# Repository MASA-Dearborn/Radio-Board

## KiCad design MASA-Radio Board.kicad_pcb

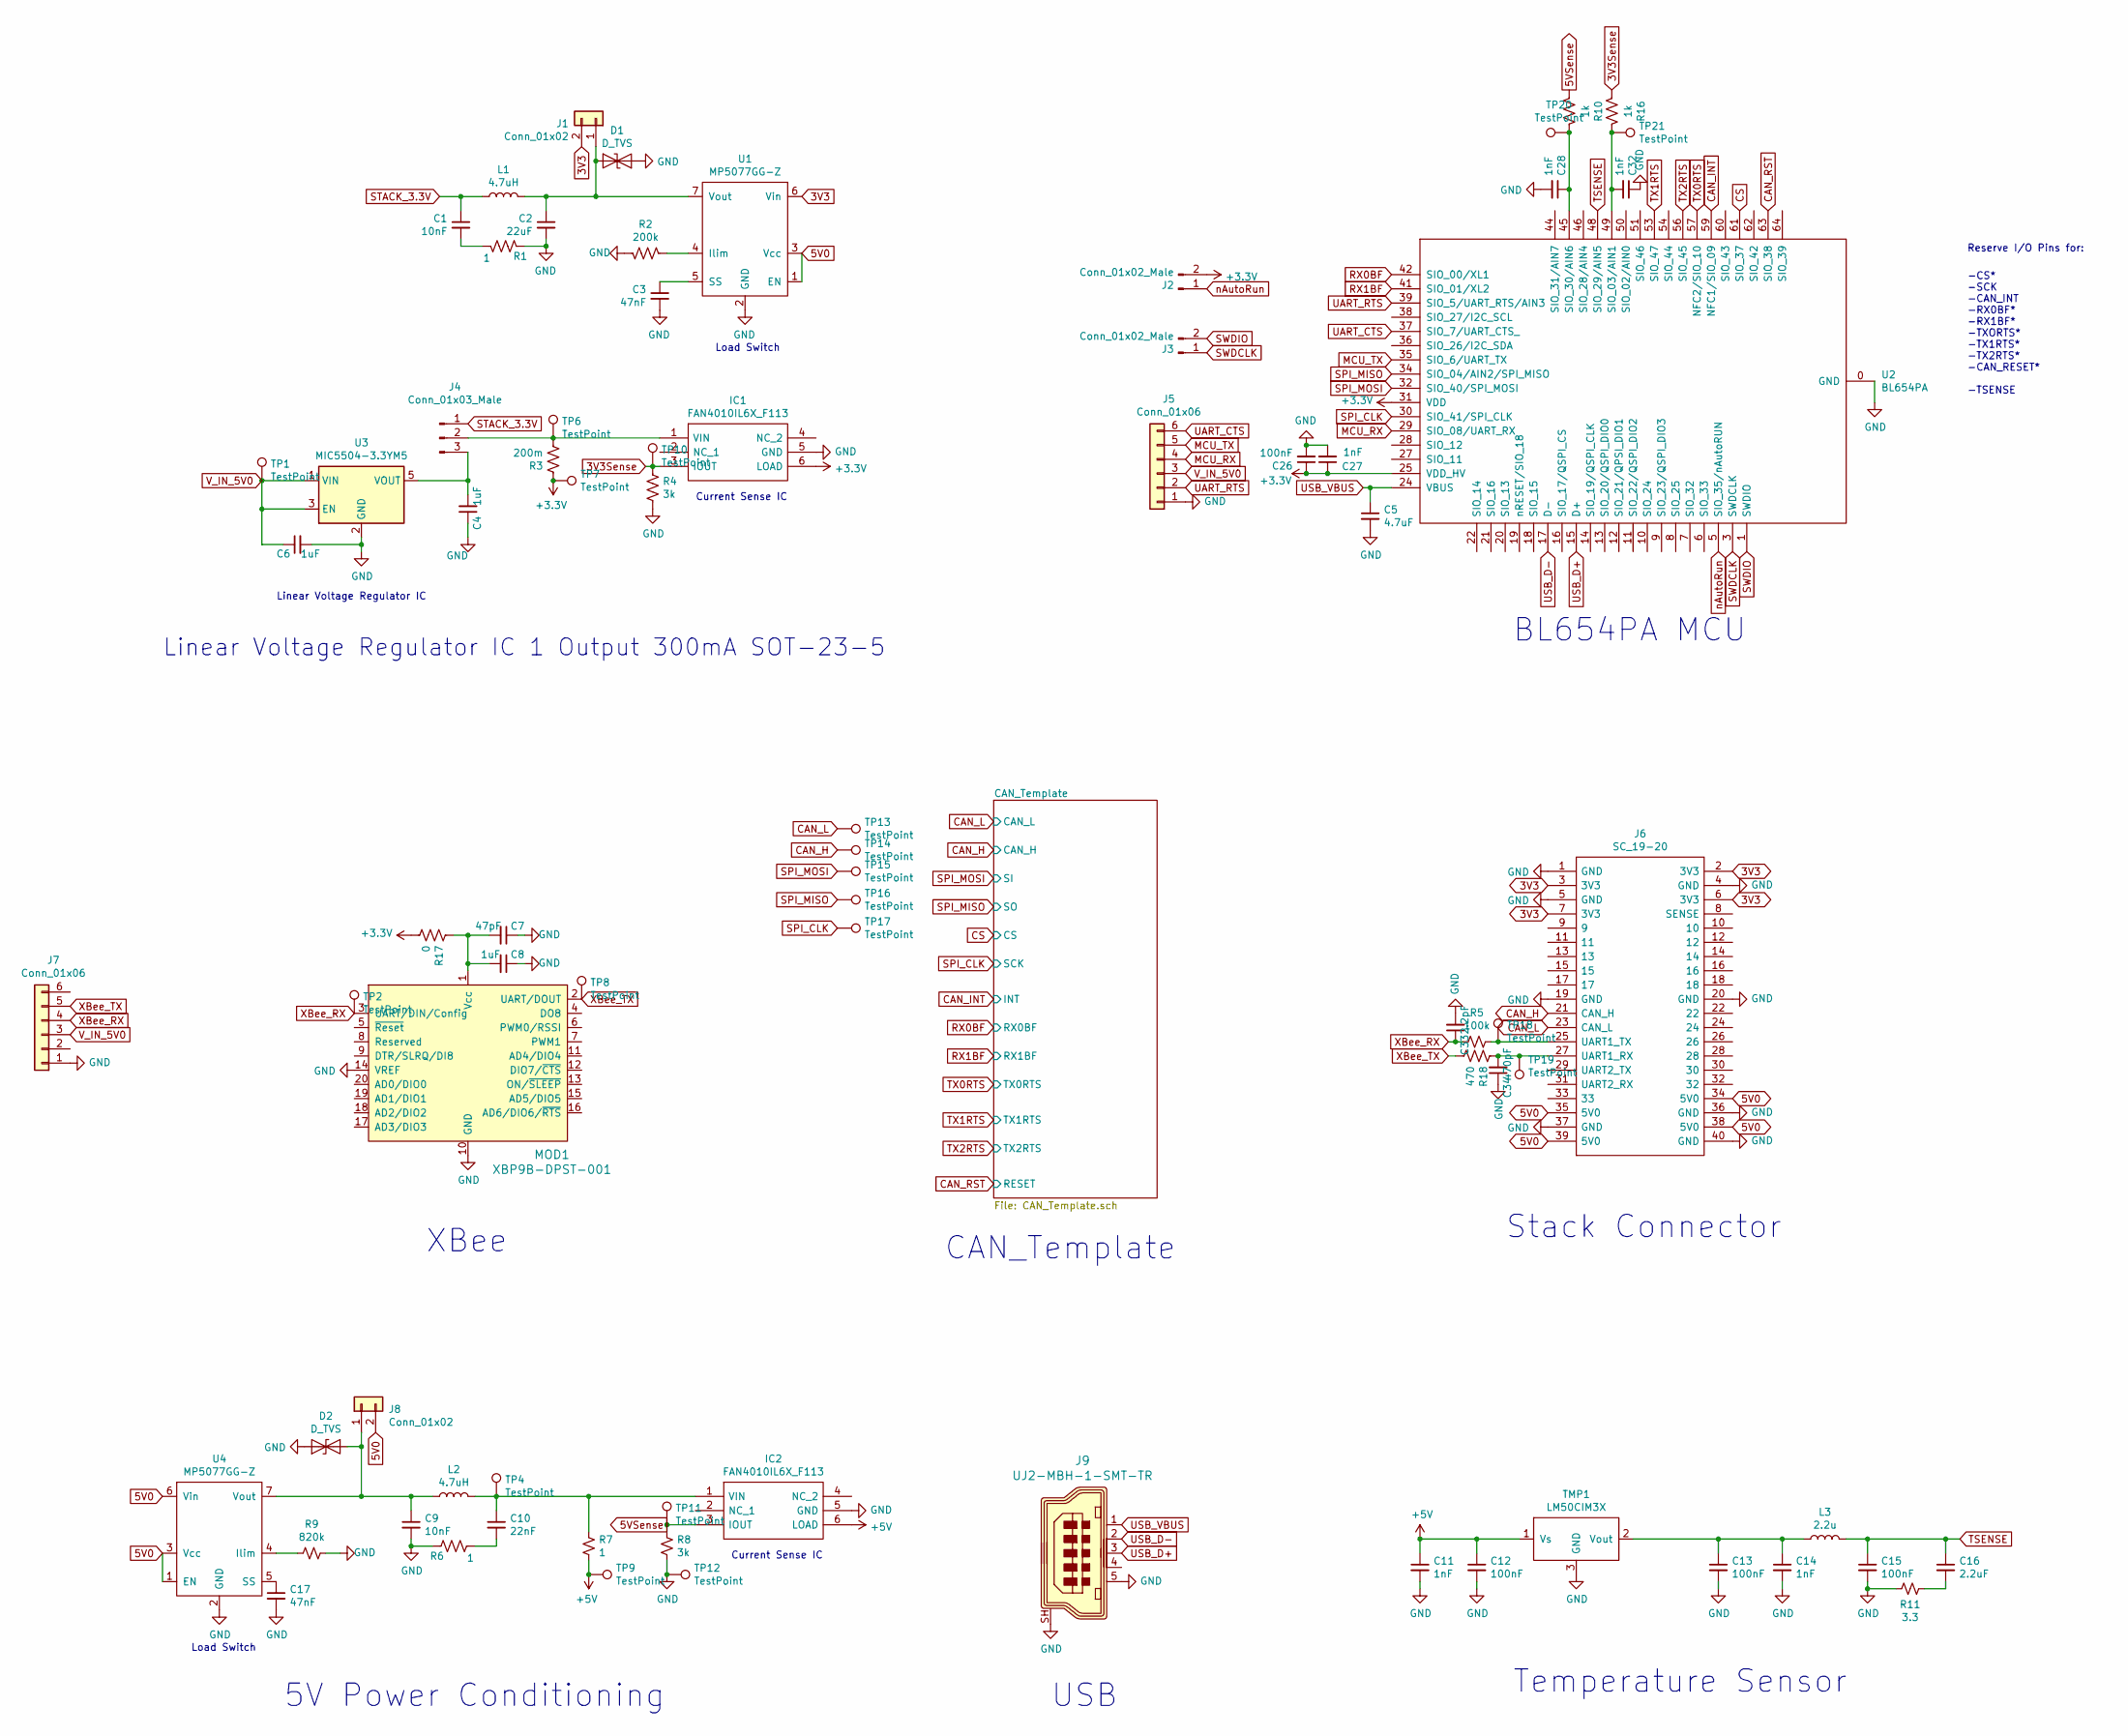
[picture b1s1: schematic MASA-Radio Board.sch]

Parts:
C1, C9: 10nF; C_0402_1005Metric
C2: 22uF; C_0603_1608Metric
C3, C17: 47nF; C_0603_1608Metric
C4, C6, C8: 1uF; C_0603_1608Metric
C5: 4.7uF; C_0603_1608Metric
C7: 47pF; C_0603_1608Metric
C10: 22nF; C_0603_1608Metric
C11, C14, C27: 1nF; C_0603_1608Metric
C12, C13, C15, C26: 100nF; C_0603_1608Metric
C16: 2.2uF; C_0603_1608Metric
C28, C32: 1nF; C_0402_1005Metric
C33: 2.2pF; C_0603_1608Metric
C34: 470pF; C_0603_1608Metric
D1, D2: D_TVS; D_SOD-523
IC1, IC2: FAN4010IL6X_F113; 6-LEAD_MICROPAK; Manufacturer_Part_Number FAN4010IL6X_F113; Mouser Part Number 512-FAN4010IL6X_F113
J1, J8: Conn_01x02; SolderJumper-2_P1.3mm_Open_TrianglePad1.0x1.5mm
J2, J3: Conn_01x02_Male; PinHeader_1x02_P2.54mm_Vertical
J4: Conn_01x03_Male; PinHeader_1x03_P2.54mm_Vertical
J5, J7: Conn_01x06; PinHeader_1x06_P2.54mm_Vertical
J6: SC_19-20; Stack_Connector_2019_2020; Manufacturer_Part_Number TFC-120-32-F-D-A-K-TR
J9: UJ2-MBH-1-SMT-TR; USB_Mini_B_Female_UJ2-MBH-1-SMT-TR; MPN UJ2-MBH-1-SMT-TR; Digi-Key_PN 102-4003-1-ND
L1, L2: 4.7uH; L_0805_2012Metric
L3: 2.2u; L_0603_1608Metric
MOD1: XBP9B-DPST-001; XBEE_PRO-20_THT; MPN XBP9B-DPST-001; Digi-Key_PN 602-1349-ND
R1, R7: 1; R_0603_1608Metric
R2: 200k; R_0603_1608Metric
R3: 200m; R_0603_1608Metric
R4, R8: 3k; R_0603_1608Metric
R5: 100k; R_0603_1608Metric
R6: 1; R_0402_1005Metric
R9: 820k; R_0603_1608Metric
R10, R16: 1k; R_0402_1005Metric
R11: 3.3; R_0603_1608Metric
R17: 0; R_0603_1608Metric
R18: 470; R_0603_1608Metric
TMP1: LM50CIM3X; SOT-23
TP1, TP2, TP4, TP6, TP7, TP8, TP9, TP10, TP11, TP12, TP13, TP14, TP15, TP16, TP17, TP18, TP19, TP20, TP21: TestPoint; TestPoint_Pad_1.0x1.0mm
U1, U4: MP5077GG-Z
U2: BL654PA
U3: MIC5504-3.3YM5; SOT-23-5

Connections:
3V3: J1.2, J6.2 (3V3), J6.3 (3V3), J6.6 (3V3), J6.7 (3V3), U1.6 (Vin), U1.11 (Vin)
3V3Sense: IC1.3 (IOUT), R4.1, R16.1, TP10.1
5V0: J6.34 (5V0), J6.35 (5V0), J6.38 (5V0), J6.39 (5V0), J8.2, U1.1 (EN), U1.3 (Vcc), U4.1 (EN), U4.3 (Vcc), U4.6 (Vin), U4.11 (Vin)
5VSense: IC2.3 (IOUT), R8.1, R10.1, TP11.1
CAN_H: J6.21 (CAN_H), TP14.1; also elsewhere on the board
CAN_INT: U2.59 (NFC1/SIO_09); also elsewhere on the board
CAN_L: J6.23 (CAN_L), TP13.1; also elsewhere on the board
CAN_RST: U2.63 (SIO_38); also elsewhere on the board
CS: U2.61 (SIO_37); also elsewhere on the board
GND: C2.2, C3.2, C4.1, C5.2, C6.2, C7.1, C8.1, C9.2, C11.2, C12.2, C13.2, C14.2, C15.2, C17.2, C26.2, C27.2, C28.2, C32.1, C33.2, C34.1, D1.1 (A1), D2.1 (A1), IC1.5 (GND), IC2.5 (GND), J5.1, J6.1 (GND), J6.4 (GND), J6.5 (GND), J6.19 (GND), J6.20 (GND), J6.36 (GND), J6.37 (GND), J6.40 (GND), J7.1, J9.5, J9.SH, MOD1.10 (GND), MOD1.14 (VREF), R1.1, R2.1, R4.2, R6.1, R8.2, R9.1, R11.1, TMP1.3 (GND), TP12.1, U1.2 (GND), U2.0 (GND), U2.23 (GND), U2.26 (GND), U2.33 (GND), U2.40 (GND), U2.43 (GND), U2.47 (GND), U2.52 (GND), U2.55 (GND), U2.58 (GND), U2.65 (GND), U2.66 (GND), U2.67 (GND), U2.68 (GND), U2.69 (GND), U2.70 (GND), U2.71 (GND), U2.72 (GND), U2.73 (GND), U2.74 (GND), U2.75 (GND), U2.76 (GND), U2.77 (GND), U2.78 (GND), U2.79 (GND), U3.2 (GND), U4.2 (GND); also elsewhere on the board
MCU_RX: J5.4, U2.29 (SIO_08/UART_RX)
MCU_TX: J5.5, U2.35 (SIO_6/UART_TX)
unnamed: C1.2, R1.2
unnamed: C2.1, D1.2 (A2), J1.1, L1.1, U1.7 (Vout), U1.8 (Vout), U1.9 (Vout), U1.10 (Vout)
unnamed: C3.1, U1.5 (SS)
unnamed: C4.2, J4.3, U3.5 (VOUT)
unnamed: C7.2, C8.2, MOD1.1 (Vcc), R17.1
unnamed: C9.1, D2.2 (A2), J8.1, L2.1, U4.7 (Vout), U4.8 (Vout), U4.9 (Vout), U4.10 (Vout)
unnamed: C10.1, IC2.1 (VIN), L2.2, R7.1, TP4.1
unnamed: C10.2, R6.2
unnamed: C13.1, C14.1, L3.1, TMP1.2 (Vout)
unnamed: C16.2, R11.2
unnamed: C17.1, U4.5 (SS)
unnamed: C28.1, R10.2, TP20.1, U2.45 (SIO_30/AIN6)
unnamed: C32.2, R16.2, TP21.1, U2.49 (SIO_03/AIN1)
unnamed: C34.2, J6.27 (UART1_RX), R18.1, TP19.1
unnamed: IC1.1 (VIN), J4.2, R3.2, TP6.1
unnamed: J6.25 (UART1_TX), R5.1, TP18.1
unnamed: R2.2, U1.4 (Ilim)
unnamed: R9.2, U4.4 (Ilim)
RX0BF: U2.42 (SIO_00/XL1); also elsewhere on the board
RX1BF: U2.41 (SIO_01/XL2); also elsewhere on the board
SPI_CLK: TP17.1, U2.30 (SIO_41/SPI_CLK); also elsewhere on the board
SPI_MISO: TP16.1, U2.34 (SIO_04/AIN2/SPI_MISO); also elsewhere on the board
SPI_MOSI: TP15.1, U2.32 (SIO_40/SPI_MOSI); also elsewhere on the board
STACK_3.3V: C1.1, J4.1, L1.2
SWDCLK: J3.1, U2.3 (SWDCLK)
SWDIO: J3.2, U2.1 (SWDIO)
TSENSE: C15.1, C16.1, L3.2, U2.48 (SIO_29/AIN5)
TX0RTS: U2.57 (NFC2/SIO_10); also elsewhere on the board
TX1RTS: U2.53 (SIO_47); also elsewhere on the board
TX2RTS: U2.56 (SIO_45); also elsewhere on the board
UART_CTS: J5.6, U2.37 (SIO_7/UART_CTS_)
UART_RTS: J5.2, U2.39 (SIO_5/UART_RTS/AIN3)
USB_D+: J9.3, U2.15 (D+)
USB_D-: J9.2, U2.17 (D-)
USB_VBUS: C5.1, J9.1, U2.24 (VBUS)
V_IN_5V0: C6.1, J5.3, J7.3, TP1.1, U3.1 (VIN), U3.3 (EN)
XBee_RX: C33.1, J7.4, MOD1.3 (UART/DIN/Config), R5.2, TP2.1
XBee_TX: J7.5, MOD1.2 (UART/DOUT), R18.2, TP8.1
nAutoRun: J2.1, U2.5 (SIO_35/nAutoRUN)

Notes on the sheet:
XBee
CAN_Template
BL654PA MCU
Stack Connector
Current Sense IC
Load Switch
5V Power Conditioning
USB
Temperature Sensor
Reserve I/O Pins for:
-CS* -SCK -CAN_INT -RX0BF* -RX1BF* -TXORTS* -TX1RTS* -TX2RTS* -CAN_RESET* -TSENSE
Linear Voltage Regulator IC
Linear Voltage Regulator IC 1 Output 300mA SOT-23-5

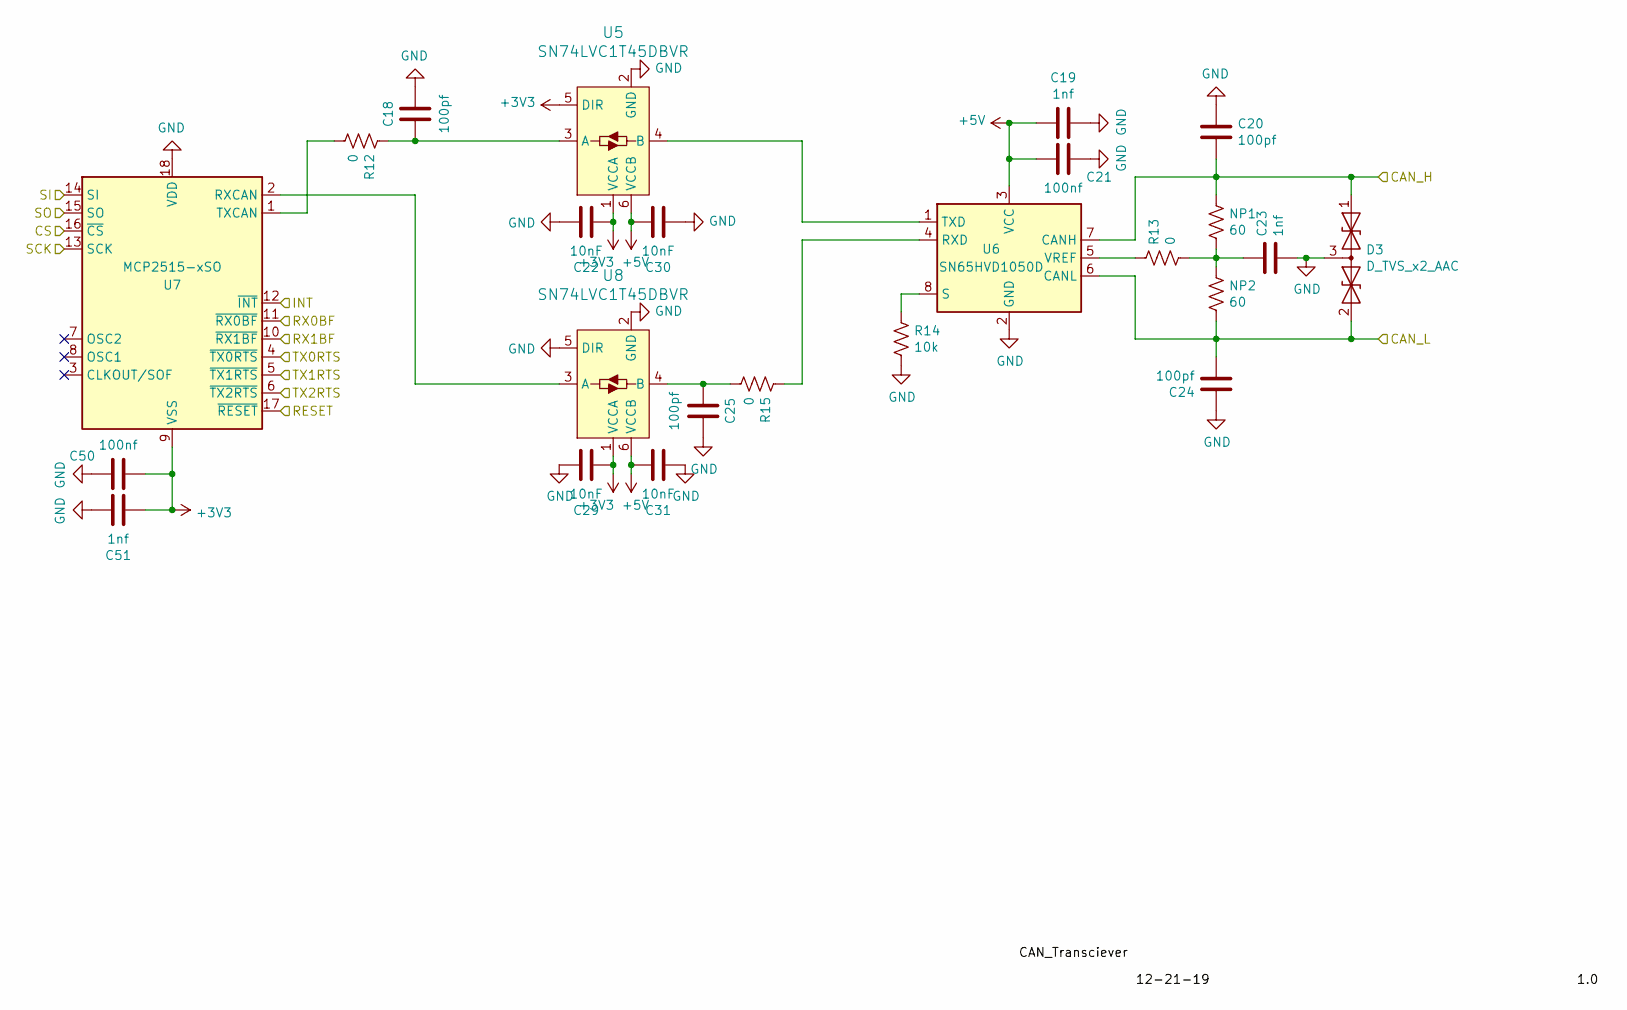
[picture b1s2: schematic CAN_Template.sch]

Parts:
C18, C20, C24, C25: 100pf; C_0603_1608Metric
C19, C23, C51: 1nf; C_0603_1608Metric
C21, C50: 100nf; C_0603_1608Metric
C22, C29, C30, C31: 10nF; C_0603_1608Metric
D3: D_TVS_x2_AAC; SOT-23
NP1, NP2: 60; R_0603_1608Metric
R12, R13, R15: 0; R_0603_1608Metric
R14: 10k; R_0603_1608Metric
U5, U8: SN74LVC1T45DBVR; SOT-23-6; MPN SN74LVC1T45DBVR; Digi-Key_PN 296-16843-1-ND
U6: SN65HVD1050D; SOIC-8_3.9x4.9mm_P1.27mm
U7: MCP2515-xSO; SOIC-18W_7.5x11.6mm_P1.27mm

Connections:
CAN_H: C20.2, D3.1 (A1), NP1.1, U6.7 (CANH); also elsewhere on the board
CAN_INT: U7.12 (~INT); also elsewhere on the board
CAN_L: C24.2, D3.2 (A2), NP2.2, U6.6 (CANL); also elsewhere on the board
CAN_RST: U7.17 (~RESET); also elsewhere on the board
CS: U7.16 (~CS); also elsewhere on the board
GND: C18.2, C19.1, C20.1, C21.2, C22.1, C23.2, C24.1, C25.2, C29.1, C30.2, C31.2, C50.2, C51.1, D3.3 (common), R14.2, U5.2 (GND), U6.2 (GND), U7.18 (VDD), U8.2 (GND), U8.5 (DIR); also elsewhere on the board
unnamed: C18.1, R12.1, U5.3 (A)
unnamed: C23.1, NP1.2, NP2.1, R13.2
unnamed: C25.1, R15.2, U8.4 (B)
unnamed: R12.2, U7.1 (TXCAN)
unnamed: R13.1, U6.5 (VREF)
unnamed: R14.1, U6.8 (S)
unnamed: R15.1, U6.4 (RXD)
unnamed: U5.4 (B), U6.1 (TXD)
unnamed: U7.2 (RXCAN), U8.3 (A)
RX0BF: U7.11 (~RX0BF); also elsewhere on the board
RX1BF: U7.10 (~RX1BF); also elsewhere on the board
SPI_CLK: U7.13 (SCK); also elsewhere on the board
SPI_MISO: U7.15 (SO); also elsewhere on the board
SPI_MOSI: U7.14 (SI); also elsewhere on the board
TX0RTS: U7.4 (~TX0RTS); also elsewhere on the board
TX1RTS: U7.5 (~TX1RTS); also elsewhere on the board
TX2RTS: U7.6 (~TX2RTS); also elsewhere on the board

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
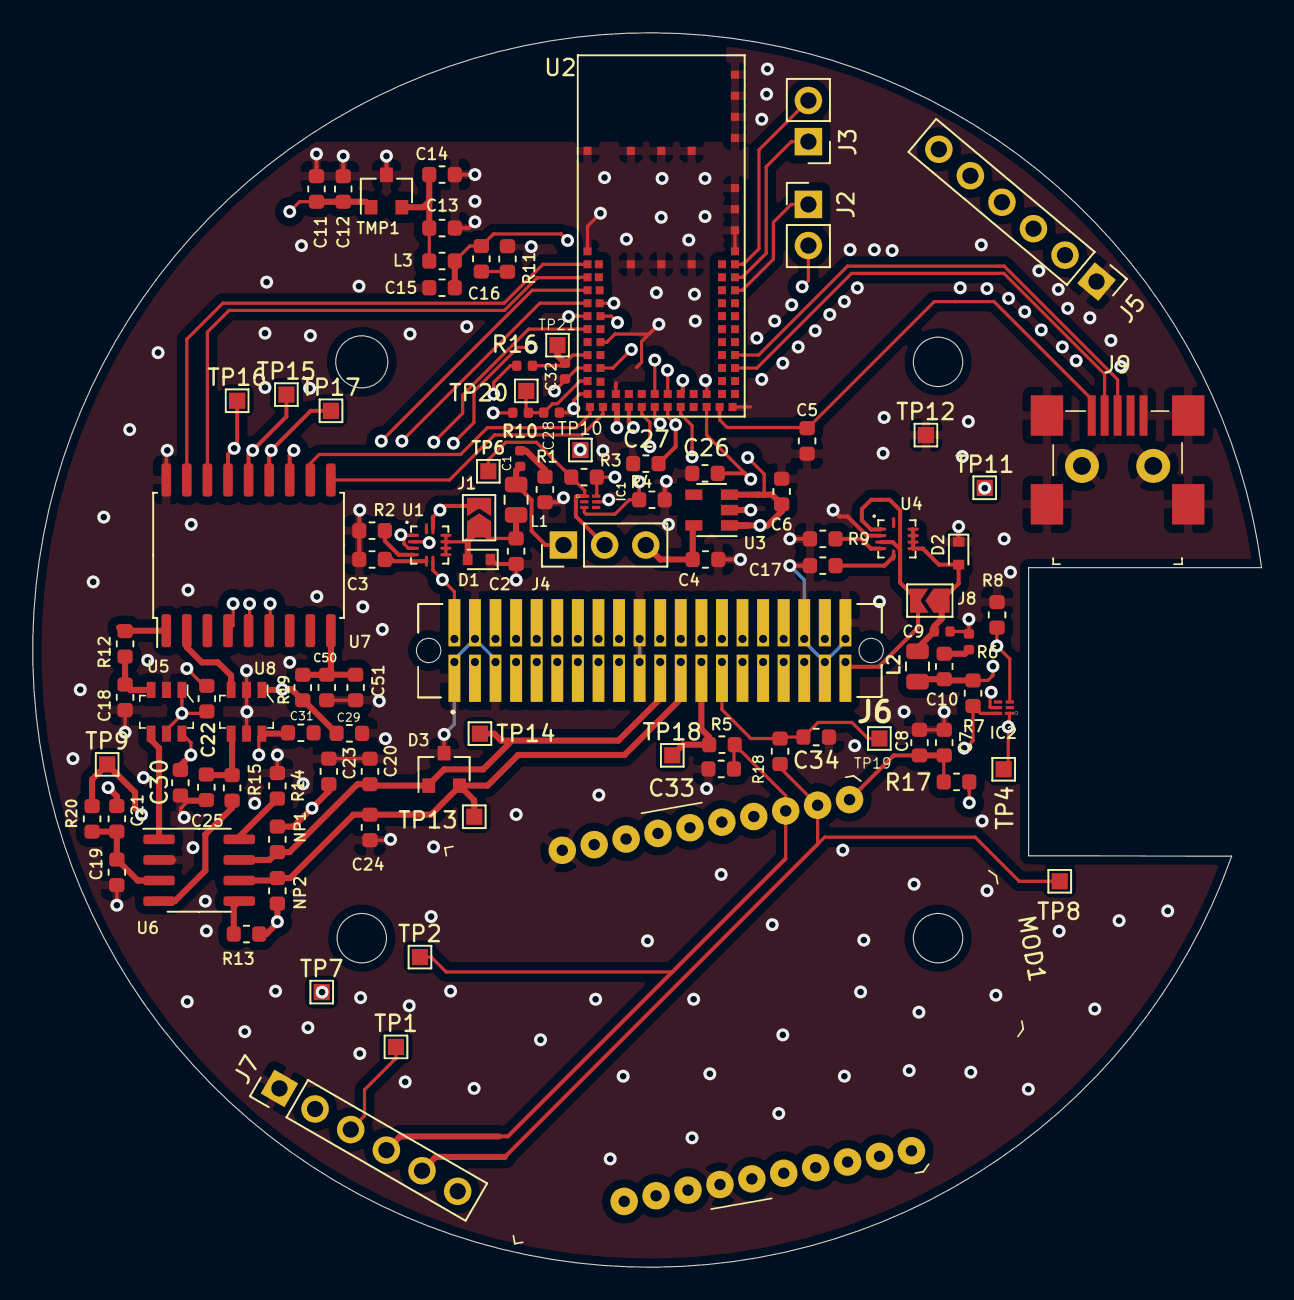
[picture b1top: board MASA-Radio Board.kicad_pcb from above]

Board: 4 copper layers, 75.8 x 76.2 mm, 104 parts (0 on the bottom side), 64 nets.

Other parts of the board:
R19, R20: 0; R_0603_1608Metric

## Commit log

2020-01-06 Completed Linear Voltage Regulator
2020-01-06 Added can to hierarchical sheet
2020-01-09 Updated connections on MCU, XBee, added headers
2020-01-09 Added stack connector and populated PCB
2020-01-12 Added 5V Power Conditioning
2020-01-12 fixed some labels
2020-01-12 Added USB Connector
2020-01-12 XBee has voltage now
2020-01-12 Modified CAN from 5.0V to 3.3V
2020-01-12 fixed/added values
2020-01-12 Connected stack to xbee
2020-01-14 Added nAutoRun header
2020-01-14 Added Temp Sensor
2020-01-14 Some minor adjustments
2020-01-14 Some more minor changes
2020-01-14 Updated R/Cap values
2020-01-16 Some minor footprint and value updates - unfinished
2020-01-16 Updated footprints, began board layout, board layers
2020-01-19 Added caps to xbee input, header to SWD pins
2020-01-22 added solder bridges, placed a few components on board
2020-01-22 Moved components
2020-01-23 A very rough placement of components, some routing
2020-01-24 Completed Most of the routing on board
2020-01-24 Some small routing changes
2020-01-24 Some I/O routing
2020-01-24 fixed tsense
2020-01-24 Added caps on 3.3V MCU
2020-01-24 Fixed caps and added grounding
2020-01-24 Removed resistor from temp sensor
2020-01-26 Added filters and connected missing analog lines. Also fixed USB
2020-01-26 Unbroke schematic
2020-01-26 Added test points
2020-01-26 Added 0 Ohm resistors
2020-01-28 Updated silk screen
2020-02-18 Fixed drc
